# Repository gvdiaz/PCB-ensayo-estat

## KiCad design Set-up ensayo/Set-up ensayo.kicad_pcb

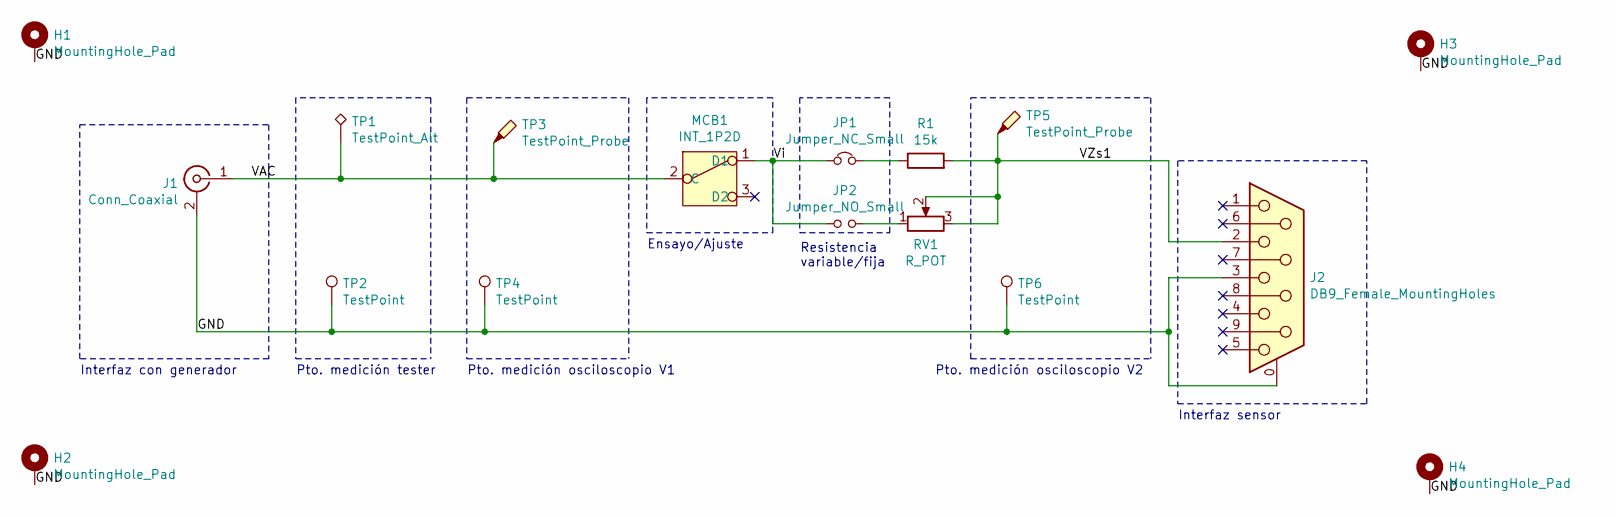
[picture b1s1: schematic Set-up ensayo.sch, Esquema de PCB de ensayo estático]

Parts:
H1, H2, H3, H4: MountingHole_Pad; MountingHole_3.2mm_M3_ISO14580_Pad
J1: Conn_Coaxial; BNC_TEConnectivity_1478204_Vertical
J2: DB9_Female_MountingHoles; DSUB-9_Female_Horizontal_P2.77x2.84mm_EdgePinOffset4.94mm_H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
JP1: Jumper_NC_Small; PinHeader_1x02_P2.54mm_Vertical
JP2: Jumper_NO_Small; PinHeader_1x02_P2.54mm_Vertical
MCB1: INT_1P2D; Switch_Toggle_ATE1D-2M3-10-Z
R1: 15k; R_Axial_DIN0204_L3.6mm_D1.6mm_P7.62mm_Horizontal
RV1: R_POT; Potentiometer_Vishay_248GJ-249GJ_Single_Vertical
TP1: TestPoint_Alt; PinHeader_1x01_P2.54mm_Vertical
TP2, TP4, TP6: TestPoint; PinHeader_1x01_P2.54mm_Vertical
TP3, TP5: TestPoint_Probe; PinHeader_1x01_P2.54mm_Vertical

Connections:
/GND: H1.1, H2.1, H3.1, H4.1, J1.2 (Ext), J2.0 (PAD), J2.3, TP2.1, TP4.1, TP6.1
/VAC: J1.1 (In), MCB1.2 (C), TP1.1, TP3.1
/VZs1: J2.2, R1.2, RV1.2, RV1.3, TP5.1
/Vi: JP1.1, JP2.1, MCB1.1 (D1)
unnamed: JP1.2, R1.1
unnamed: JP2.2, RV1.1

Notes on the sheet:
Interfaz con generador
Pto. medición tester
Pto. medición osciloscopio V1
Ensayo/Ajuste
Pto. medición osciloscopio V2
Interfaz sensor
Resistencia variable/fija

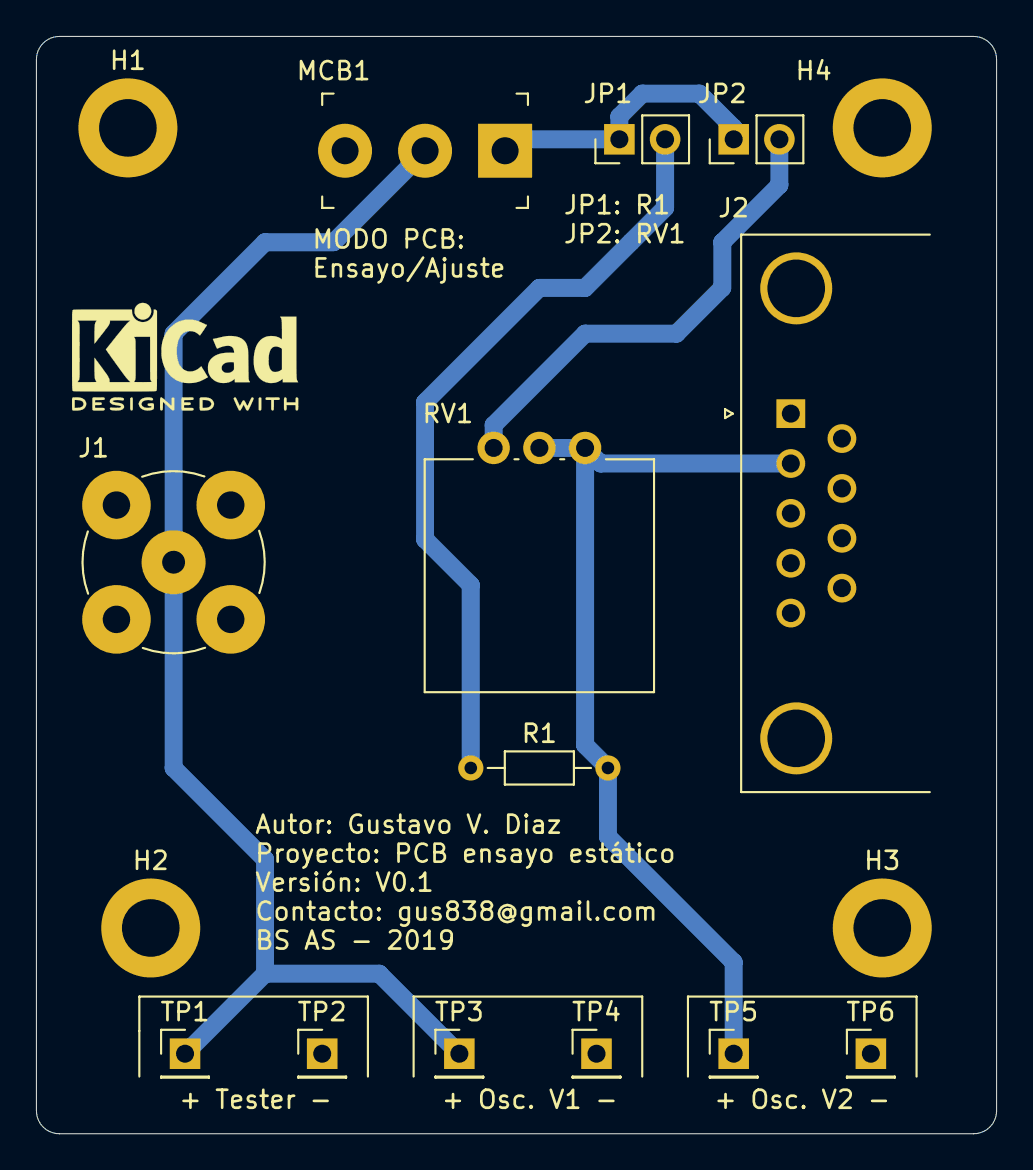
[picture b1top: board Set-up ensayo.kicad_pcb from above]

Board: 2 copper layers, 53.3 x 61.0 mm, 17 parts (0 on the bottom side), 6 nets.

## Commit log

2019-07-28 Inicio de placa para ensayo estático, usando el proceso de diseño de esquemático estoy por el paso 1 (setup)
2019-08-01 Terminé con el paso 1 de proceso y comencé con el paso 2 colocando componentes, falta el interruptor para cambiar de estado del PCB (ensayo/configuración)
2019-08-02 Cree componente circuit breaker en librería nueva Simbolo-ensayo y comencé a colocar los símbolos de los componentes
2019-08-05 Agregué puntos de pruebas y campo de función en cada componente del esquema, fin de segundo paso en proceso
2019-08-05 Paso 3 de proceso de diseño, agrupé a los componentes por función y les puse designador. Queda pendiente asociar a footprints pero debo contar con un calibre para verificarlos
2019-08-06 Terminé con el 3er paso del proceso de diseño de esquemático. Cada componente tiene su footprint pero hay que vericarlo
2019-08-07 Pasos 4 y 5 del proceso de diseño de esquemático hechos
2019-08-07 Paso 6 (ERC) de proceso de diseño de esquemático hecho
2019-08-07 Paso 7 (agregar gráfico a esquema) y paso 8 (generar netlist PCB) de proceso de diseño de esquemático hechos, resta verificar footprints pendientes
2019-08-07 Nueva placa footprints
    Intenté generar una nueva placa que solo tenga los footprints elegidos para testearlos con un impresión. No pude hacerlo porque las librerías que tengo en esta pc son diferentes a las que tengo en la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
2019-08-08 Generación de archivo para verificar footprints de PCBs
2019-08-11 Dejo de seguir al archivo fp-info-cache dada la intrascendencia
2019-08-12 Modificaciones a esquemático, cambié los footprints de cada componente. Los cree en una librería propia
2019-08-12 Librería propia creada con los footprints propios para no depender de las librerías de kicad
2019-08-13 Modificación en footprint de switch, al fin modificado
2019-08-13 Modificación en page settings y actualización de fecha de modificación
2019-08-13 Actualización del archivo .net que toma datos de la librería creada por mí par este proyecto
2019-08-13 Paso 1 inconcluso de proceso de diseño de PCB, queda especificar las reglas de diseño para terminar este paso
2019-08-14 Agregué al esquemático un potenciómetro variable y su footprint en paralelo a R de ensayo en caso de que necesite ser variada
2019-08-14 Agregado de footprint de potenciómetro a PCB
2019-08-15 Agregué pines para configuración de resistencia variable o fija para ensayo
2019-08-15 Agregué footprint de jumper de configuración a biblioteca de footprints
2019-08-15 Agregué los nuevos componentes importados desde el esquemático
2019-08-15 Modificación de fecha en plano de esquema
2019-08-15 Cambié posición de un nodo por prolijidad
2019-08-15 Terminé con paso 1 de proceso de diseño de PCB, quedaron revisadas las reglas de diseño de PCB
2019-08-15 Empecé con el 2do paso del proceso de diseño de PCB, definí el tamaño del PCB 60x60mm2, queda pendiente hacer los bordes redondeados, ja
2019-08-16 PCB con bordes redondeados
2019-08-16 Terminé 2do y 3er paso en proceso de diseño de PCB
2019-08-16 Comencé con el paso 4 del proceso de diseño de PCB pero debo verificar el footprint de los pines, creo que es un footprint muy chico
2019-08-20 Agrego archivos a biblioteca de footprints para cambiar el footprint de los pines de 1mm por los de 2,54 mm
2019-08-20 Cambié los footprints en el archivo .net y en el esquemático
2019-08-20 Cambié los footprints pero son demasiado grandes para colocar los que son horizontales, los voy a cambiar por verticales
2019-08-20 Cambio de footprint horizontal por verticales para pines de medicion y ruteo de las pistas correspondientes
2019-08-20 Saqué los archivos de la biblioteca que no utilizo mas
2019-08-20 Se me había pasado sacar este footprint también de la biblioteca de proyecto
2019-08-20 Actualizción de archivos de footprints
2019-08-21 5to paso de proceso de diseño de PCB finalizado
2019-08-21 Modifiqué ubicación notación de componentes relativa a ellos, arriba y a la izquierda
2019-08-21 Finalicé 6to paso de proceso de diseño de PCB
2019-08-21 Finalicé 7mo paso de proceso de diseño de PCB
2019-08-21 Agregué archivo para imprimir vista de PCB final y ya mandarlo a fabricar
2019-08-23 Exportación de archivos
    Creación de archivos para realizar la placa.
2019-08-26 Creación de máscara de silkscree para generar la mascara por mí mismo.
2019-08-27 Modificación de footprint mal diseñado, los agujeros son muy chicos, lo verifiqué con el PCB fabricado
2019-08-27 Ya había configurado este archivo para que no aparezca pero sigue apareciendo
2019-08-27 Cambié el footprint en el PCB para que no haya problemas en el futuro
